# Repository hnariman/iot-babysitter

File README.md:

# About

Overall idea of the project is to build IoT Babysitter 

Problem it solves: my personal issue "make sure I don't miss baby crying, when I wear headset" 

& demonstration of basic interaction with AWS IoT and Mobile phones.

** maybe could be usefull for fire/intrusion alarms as well

## Requirements:
On any abnormal level of sound which mic is registering (baby starts to cry),
this portable device shall send SMS Text notification to group of people
(family members).

## Diagram:
```mermaid
sequenceDiagram
participant Mic
participant Device
participant AWS IoT
participant SNS Topic
participant Mobile Phone

Mic->>Device: registers noise level above the limit
Device->>AWS IoT: sends request with data (maybe dbs of sound or 1 to 10 level of noise) 
AWS IoT->>SNS Topic: sends data from request
SNS Topic->>Mobile Phone: sends text message to group saying "baby is crying"
```

## Hardware:
- ESP32 based WEMOS D1 mini (compact and has all what we need) [Documentation](https://www.wemos.cc/en/latest/d1/d1_mini.html) 

- Adafruit MAX9814 microphone with built in Amplifier [DataSheet](https://cdn-shop.adafruit.com/datasheets/MAX9814.pdf)
 
- Some power (not sure yet maybe a battery, maybe some AC/DC converter to plug the device into socket)

## Software:
- AWS CDK IaC project to configure necessary permissions and setup (IoT Thing & SNS)
- Bash/Python script ( AWS Cli ) to grab necessary device certificates and store on github in this repo
- C++ code for ESP32 (also including reading and using ENV variables and Certificates before - maybe done by some python code)

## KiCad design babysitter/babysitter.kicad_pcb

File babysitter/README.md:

# About

Basic hardware design for Babysitter IoT device.

Wemos D1 Mini is still not delivered, so I will use ESP32-WROOM-32 devboard for now.

## PCB:

## Schematics:

## 3D (lib seem to be broken)

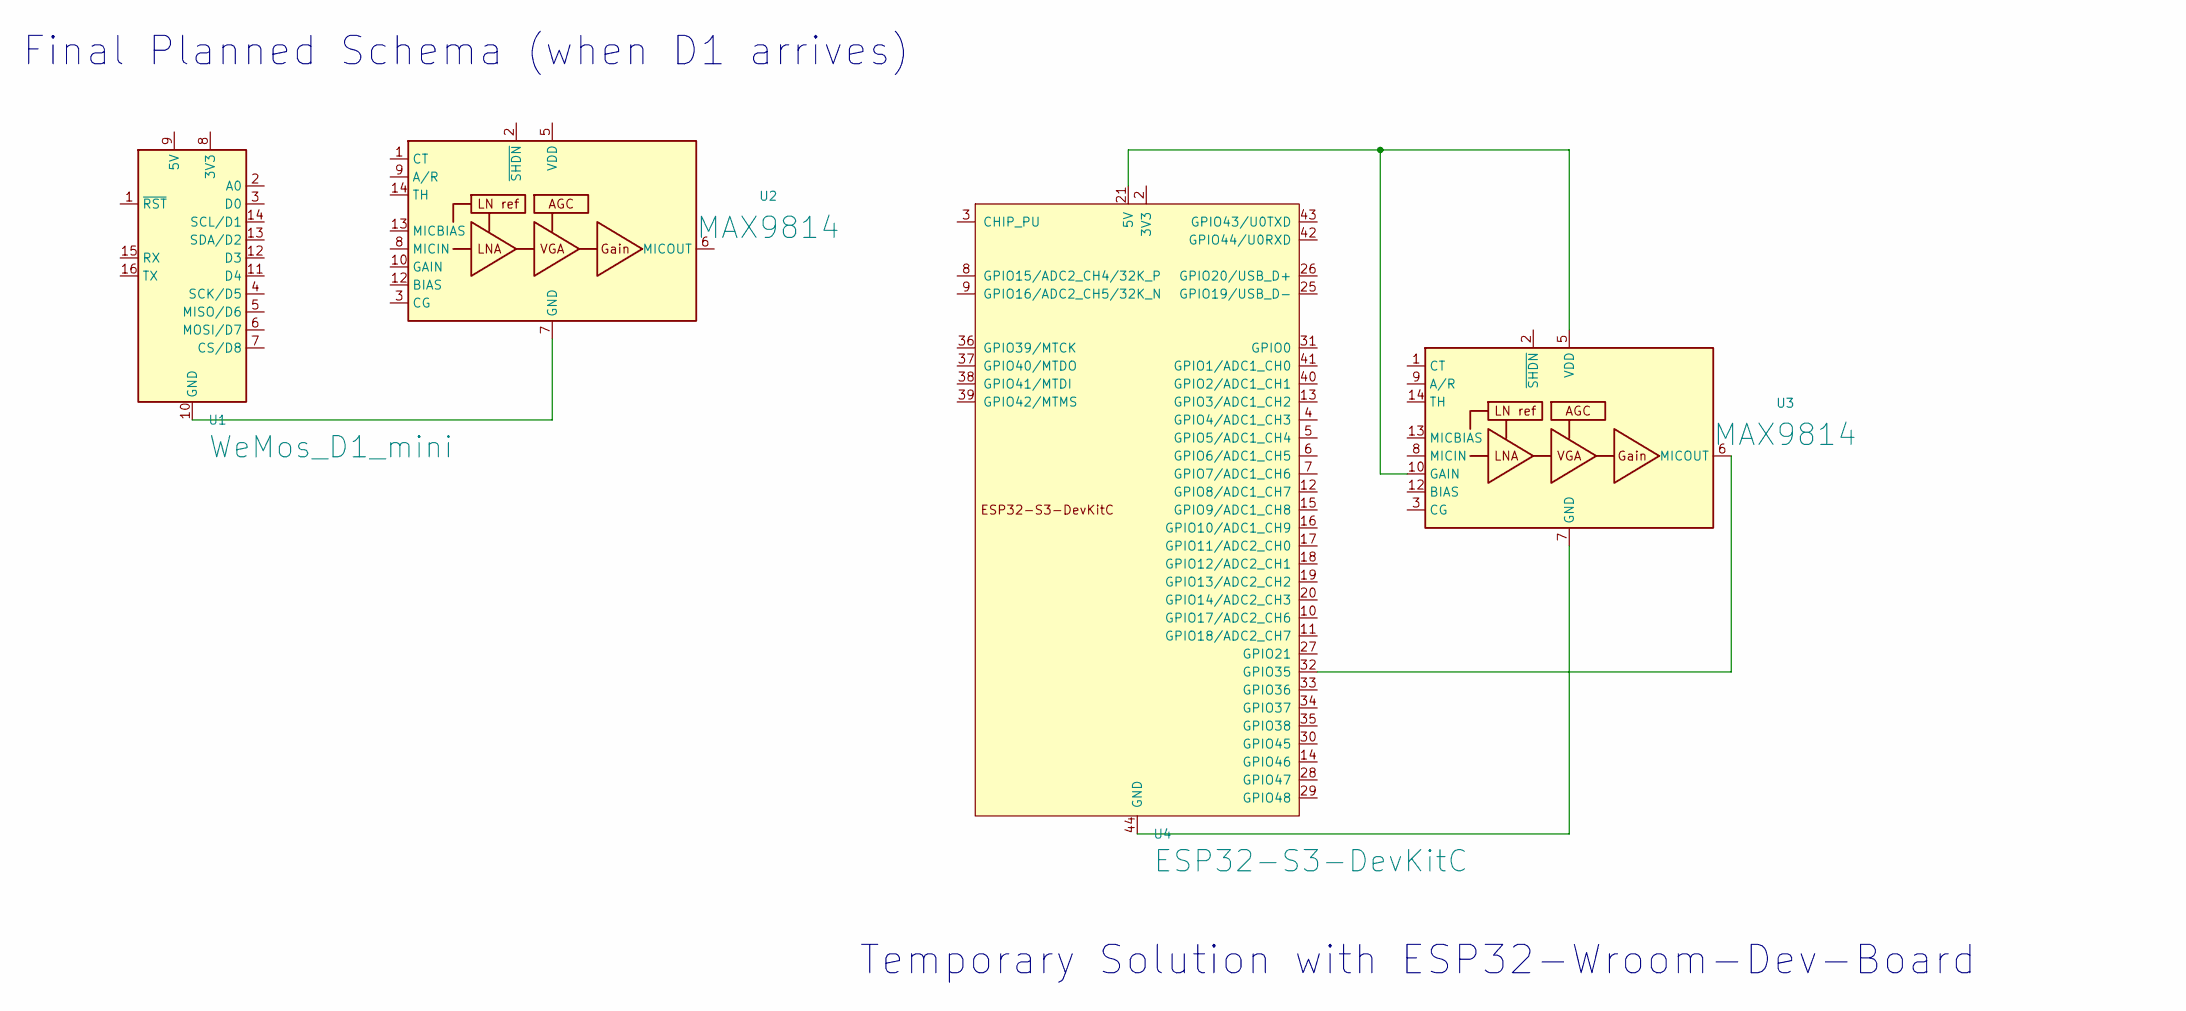
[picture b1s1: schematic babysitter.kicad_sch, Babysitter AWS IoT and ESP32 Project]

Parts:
U1: WeMos_D1_mini; WEMOS_D1_mini_light
U2, U3: MAX9814; DFN-14-1EP_3x3mm_P0.4mm_EP1.78x2.35mm
U4: ESP32-S3-DevKitC

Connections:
unnamed: U1.10 (GND), U2.4 (GND), U2.7 (GND), U2.11 (GND), U2.15 (GND)
unnamed: U3.5 (VDD), U3.10 (GAIN), U4.21 (5V)
unnamed: U3.4 (GND), U3.7 (GND), U3.11 (GND), U3.15 (GND), U4.22 (GND), U4.23 (GND), U4.24 (GND), U4.44 (GND)
unnamed: U3.6 (MICOUT), U4.32 (GPIO35)
unnamed: U4.1 (3V3), U4.2 (3V3)

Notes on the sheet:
Temporary Solution with ESP32-Wroom-Dev-Board
Final Planned Schema (when D1 arrives)

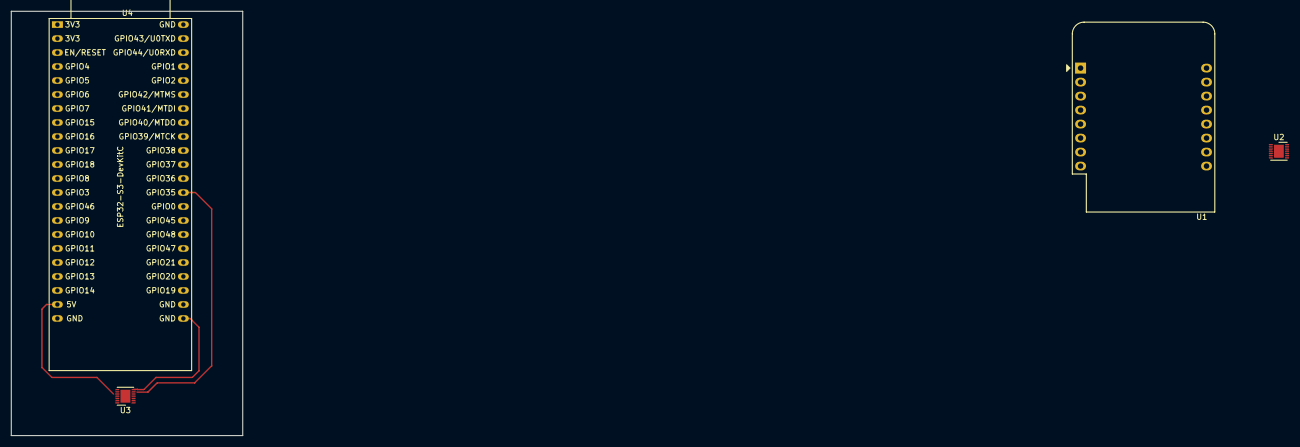
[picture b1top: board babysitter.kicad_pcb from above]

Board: 2 copper layers, 42.0 x 77.0 mm, 4 parts (0 on the bottom side), 5 nets.

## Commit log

2023-12-02 added readme
2023-12-02 updated readme with links
2023-12-02 updated image size in readme and links"
2023-12-02 fixed broken link
2023-12-02 Updated readme with datasheeet for MAX9814
2023-12-02 added KiCad files
2023-12-02 updated images and added readme for KiCad files
2023-12-02 removed image size from KiCad readme
2023-12-02 datsheet link issue
